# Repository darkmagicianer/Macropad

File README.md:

# Macropad

## PCB

DRC has no errors listed

## CAD

## Firmware
The macro keys are programmed right now to copy, paste, and do a small run and stop running macro for video games.

## BOM
- Seeed XIAO RP2040 microcontroller
- 6x hackpad switches
- 6x hackpad keycaps
- 4x M3x16mm screws
- 4x M3x5mx4mm heatset inserts

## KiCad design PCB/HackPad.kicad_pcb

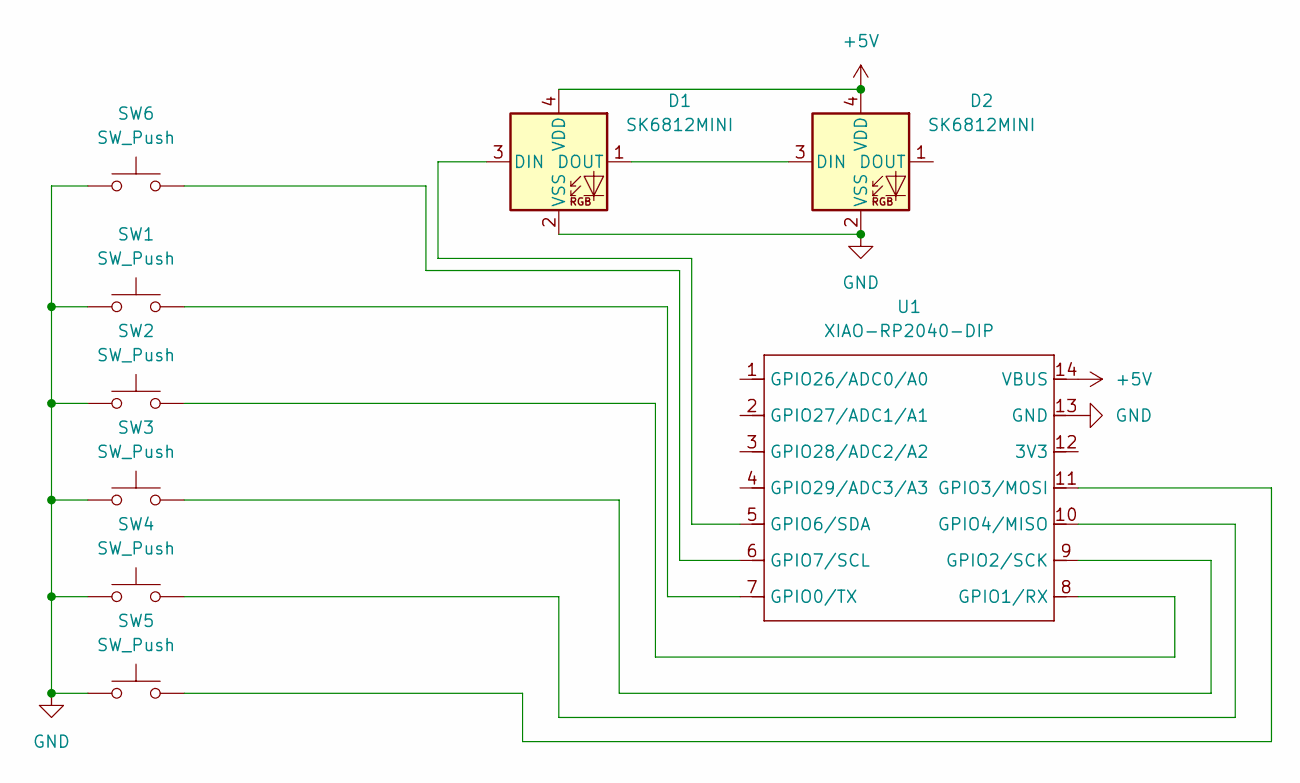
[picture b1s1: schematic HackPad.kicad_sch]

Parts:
D1, D2: SK6812MINI; LED_SK6812MINI_PLCC4_3.5x3.5mm_P1.75mm
SW1, SW2, SW3, SW4, SW5, SW6: SW_Push; SW_Cherry_MX_1.00u_PCB
U1: XIAO-RP2040-DIP

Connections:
+5V: D1.4 (VDD), D2.4 (VDD), U1.14 (VBUS)
GND: D1.2 (VSS), D2.2 (VSS), SW1.1, SW2.1, SW3.1, SW4.1, SW5.1, SW6.1, U1.13 (GND)
unnamed: D1.3 (DIN), U1.5 (GPIO6/SDA)
unnamed: D1.1 (DOUT), D2.3 (DIN)
unnamed: SW1.2, U1.7 (GPIO0/TX)
unnamed: SW2.2, U1.8 (GPIO1/RX)
unnamed: SW3.2, U1.9 (GPIO2/SCK)
unnamed: SW5.2, U1.11 (GPIO3/MOSI)
unnamed: SW4.2, U1.10 (GPIO4/MISO)
unnamed: SW6.2, U1.6 (GPIO7/SCL)

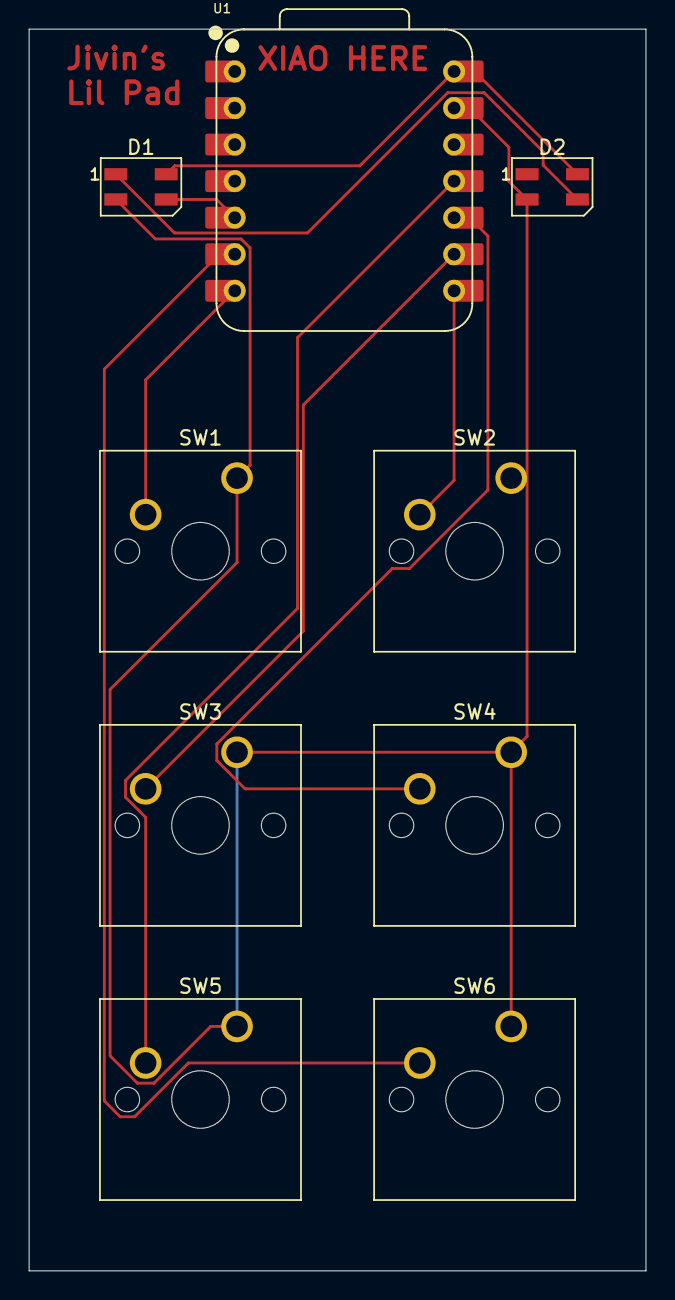
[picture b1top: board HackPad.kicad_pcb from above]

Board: 2 copper layers, 42.9 x 86.3 mm, 9 parts (0 on the bottom side), 10 nets.

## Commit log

2026-06-02 CAD/
2026-06-02 Add initial content to CAD/readme
2026-06-02 Add new file ha with initial content
2026-06-02 Create ha
2026-06-02 Enhance README with detailed project information
    Expanded README with sections on PCB, CAD, Firmware, and BOM.
